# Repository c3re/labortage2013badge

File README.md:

# HOTP-USB-Generator / labortage2013badge
http://www.das-labor.org/wiki/LaborTageBadge2013

This is a fork of LaborTageBadge2013 from Das Labor in Bochum. This Project is, as of now, 4 years old and hasn't been touched since.
I forked the project and changed the Pins of the USB-Data Pins and altered the Code in a way that 3 tokens are sent immediately after
insertion of the USB-Stick. With the Pin Header modification you can flash the software onto a Digispark Digistump which costs 1-2$ per piece.
In addition to that i added a 3d-case stl-file which was designed by a c3re-member (thx et merci).

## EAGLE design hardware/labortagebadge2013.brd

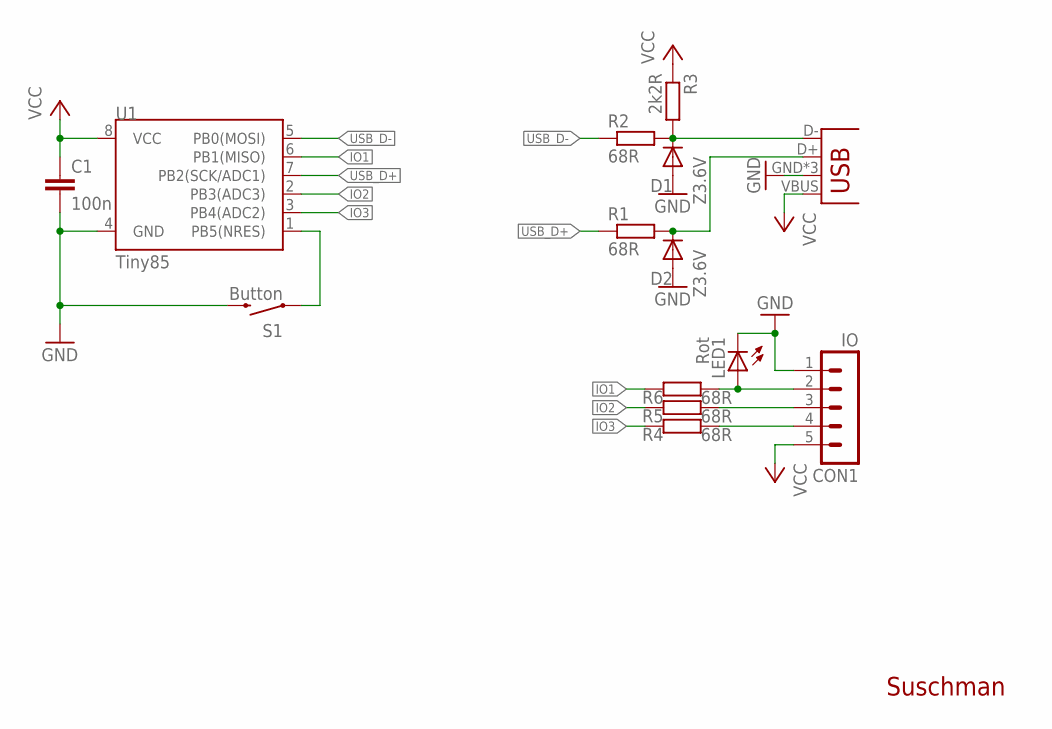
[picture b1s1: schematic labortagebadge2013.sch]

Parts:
C1: 100n; C0805
CON1: IO; MA05-1
D1, D2: Z3.6V; MINIMELF
LED1: Rot; CHIPLED_0805
R1, R2, R4, R5, R6: 68R; R0805
R3: 2k2R; R0805
S1: Button; TACTILE_SWITCH_TALL
U1: Tiny85; SO08-EIAJ
USB-A: USB-A; USB-A-H

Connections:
GND: C1.2, CON1.1, D1.A, D2.A, LED1.C, S1.B1 (2), S1.B2 (2), U1.4 (GND), USB-A.GND (VBUS), USB-A.GND2 (VBUS), USB-A.GND3 (VBUS)
IO1: R6.1, U1.6 (PB1(MISO))
IO2: R5.1, U1.2 (PB3(ADC3))
IO3: R4.1, U1.3 (PB4(ADC2))
unnamed: D2.C, R1.2, USB-A.D+ (D-)
unnamed: S1.A1 (1), S1.A2 (1), U1.1 (PB5(NRES))
unnamed: CON1.4, R4.2
unnamed: CON1.3, R5.2
unnamed: CON1.2, LED1.A, R6.2
unnamed: D1.C, R2.2, R3.2, USB-A.D- (D+)
USB_D+: R1.1, U1.7 (PB2(SCK/ADC1))
USB_D-: R2.1, U1.5 (PB0(MOSI))
VCC: C1.1, CON1.5, R3.1, U1.8 (VCC), USB-A.VBUS (GND)

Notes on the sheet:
Suschman

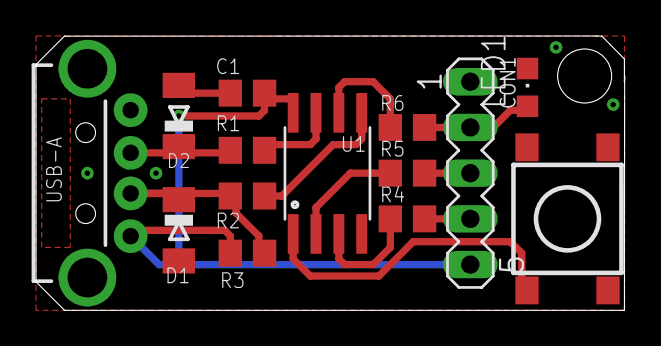
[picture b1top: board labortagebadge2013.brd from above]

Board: 2 copper layers, 32.7 x 15.2 mm, 14 parts (0 on the bottom side), 13 nets.

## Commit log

2015-01-03 initial - non working - stuff
    initial - non working - stuff
2015-01-03 adding old command-line-tool
    adding old command-line-tool
2015-01-03 keyboard functionality still not working
    keyboard functionality still not working
2015-01-03 can send a keypress
    can send a keypress
2015-01-03 removing color stuff; introducing debug stuff
    removing color stuff; introducing debug stuff
2015-01-03 removing color stuff; introducing debug stuff (cmd)
    removing color stuff; introducing debug stuff (cmd)
2015-01-03 removing warnings for cmd-tool
    removing warnings for cmd-tool
2015-01-03 adding bootloader
    adding bootloader
2015-01-03 many new features, but a bit to big
    many new features, but a bit to big
2015-01-03 this should work
    this should work
2015-01-03 a bit smaller
    a bit smaller
2015-01-03 all the forgotten files
    all the forgotten files
2015-01-03 switching to simple counter variant
    switching to simple counter variant
2015-01-03 removing temperature feature
    removing temperature feature
2015-01-03 removing memory r/w/x features
    removing memory r/w/x features
2015-01-03 removing unneeded character entering capability
    removing unneeded character entering capability
2015-01-03 whitespace editing / typo correction
    whitespace editing / typo correction
2015-01-03 comment editing
    comment editing
2015-01-03 minor optimiztion
    minor optimiztion
2015-01-03 some minor editings
    some minor editings
2015-01-03 modifying cmd-tool for new commands
    modifying cmd-tool for new commands
2015-01-03 removing old commands from cmd-tool
    removing old commands from cmd-tool
2015-01-03 seems to be working ok
    seems to be working ok
2015-01-03 some minor fixes
    some minor fixes
2015-01-03 adding hardware files
    adding hardware files
2015-01-03 adding final hex file for those who do not like compiling
    adding final hex file for those who do not like compiling
2015-01-03 small bug-fix
    small bug-fix
2018-06-28 changed usb-pins, stick fires three tokens at once immideately aftern insertion, minor makefile changes, added 3D-Case

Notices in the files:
parts and their libraries:
SparkFun-DigitalIC: Licensing: CC v3.0 Share-Alike You are welcome to use this library for commercial purposes.
